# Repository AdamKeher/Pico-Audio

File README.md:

# picoAUDIO
The audio solution dedicated to the TinyPICO.

Arduino Support Library: https://github.com/AdamKeher/Pico-Audio-Arduino

3d printable base: https://github.com/AdamKeher/Pico-Audio/tree/master/base
## About
The picoAUDIO is a fully featured audio solution specially made for the TinyPICO ESP32 development board, featuring an I2S Stereo DAC, I2S Mono MEMS Microphone, builtin 3.7W Stereo Amplifier, dedicated Headphone Amplifier, I2C GPIO Extender and built-in MicroSD card reader.

We utilise a low power NXP UDA1334A IC featuring a clear digital 16/20/24 bit, 44.1kHz, stereo audio DAC. Accompanying the DAC is a Knowles SPH0645 I2S digital mono microphone. This miniature low power MEMS microphone provides a low noise, 24 bit, 44.1kHz stream. Complimenting the DAC is the powerful Maxim MAX98306 3.7W stereo class D amplifier with stero speaker terminals and a Texas Instrumets TPA6132A2 stereo headphone amplifier with 3.5mm audio jack.

A simple mounting socket hosts the TinyPICO development board and connects all of these great features together in a seamless and easy to utilise footprint measuring a tiny 33 mm x 57 mm (1.29in x 2.24in). To provide maximum connectivity the board features a built-in MicroSD card reader and GPIO extender to hookup 8 inputs and outputs for all of your button and LED needs.
## PCB Layout

## Features
The software and hardware used in this project have been made possible by the principle of open hardware and software. Many of the samples have been collected together from a variety of authors and modified to work out of the box with the picoAUDIO for instructional purposes. Please consult each sample project for relevant license and credit.
## Features
* TinyPICO Compatible
  * Simply plug your TinyPICO board into the picoAUDIO and your ready to go
* Audio Out
  * Dedicated Texas Instruments headphone amplifier for distortion free audio.
  * 3.5mm headphone jack. Plug in headphones or line out to an external device.
  * Stereo screw clamp audio terminals. The speaker terminals automatically mute when the 3.5mm jack is used.
* Built-in MicroSD Card
  * Quality Molex mechanism
  * Simple SPI interface
  * Activity LED light
  * Push-Push socket with overhanging edge mounted card for easy insertion
* UDA1334A Stereo DAC
  * Low power audio DAC
  * Integrated digital filter and switchable digital de-emphasis for 44.1 kHz frequency
  * Supports samples from 16 to 100 kHz
  * Simple I2S interface
  * 16/20/24 bit audio
  * High linearity, wide dynamic range and low distortion
* MAX98306 Stereo Amplifier
  * Low power efficient operation
  * 3.7W @ 3Ohm, 10% THD / 1.7W at 8Ohm, 10% THD
  * Spread Spectrum Modulation
  * Five selectable gain levels
  * Excellent click and pop suppression
* TPA6132A2 Headphone Amplifier
  * 25mW Headphone Amplifier for 16/32Ω Headphones with 3.5mm Audio Jack  
  * Unlike most audioboards, the picoAUDIO features a dedicated headphone amplifer
  * Doesn't use caps to drive headphone audio, reducing unwanted noise and distortion
  * Click and pop supression
  * Low power amplifier @ 2.1mA typical supply current
  * Four selectable gain levels
* SPH0645LM4H MEMS Microphone
  * Low power design
  * Simple I2S interface
  * Flat frequency response
  * 24 bit, 44.1kHz audio
  * High SNR of 65dB(A)
  * RF shielded
  * Omnidirectional
* PCF8574 GPIO Extender
  * Low standby current
  * I2C programmable
  * Latched outputs with enough current to drive LEDs
  * 8 Input and Output ports wired to a header with 3 outputs also pre wired to onboard buttons.
## Sample Projects Modified for picoAUDIO
* Stream net radio stations with MP3 support
  * I2C 2x16 character LCD and ILI93411 320x240 TFT display samples provided
* Play audio from SD card with MP3 support
* Record audio to SD card
* Realtime full duplex audio. Vocoder example receives from mic and playback from DAC.

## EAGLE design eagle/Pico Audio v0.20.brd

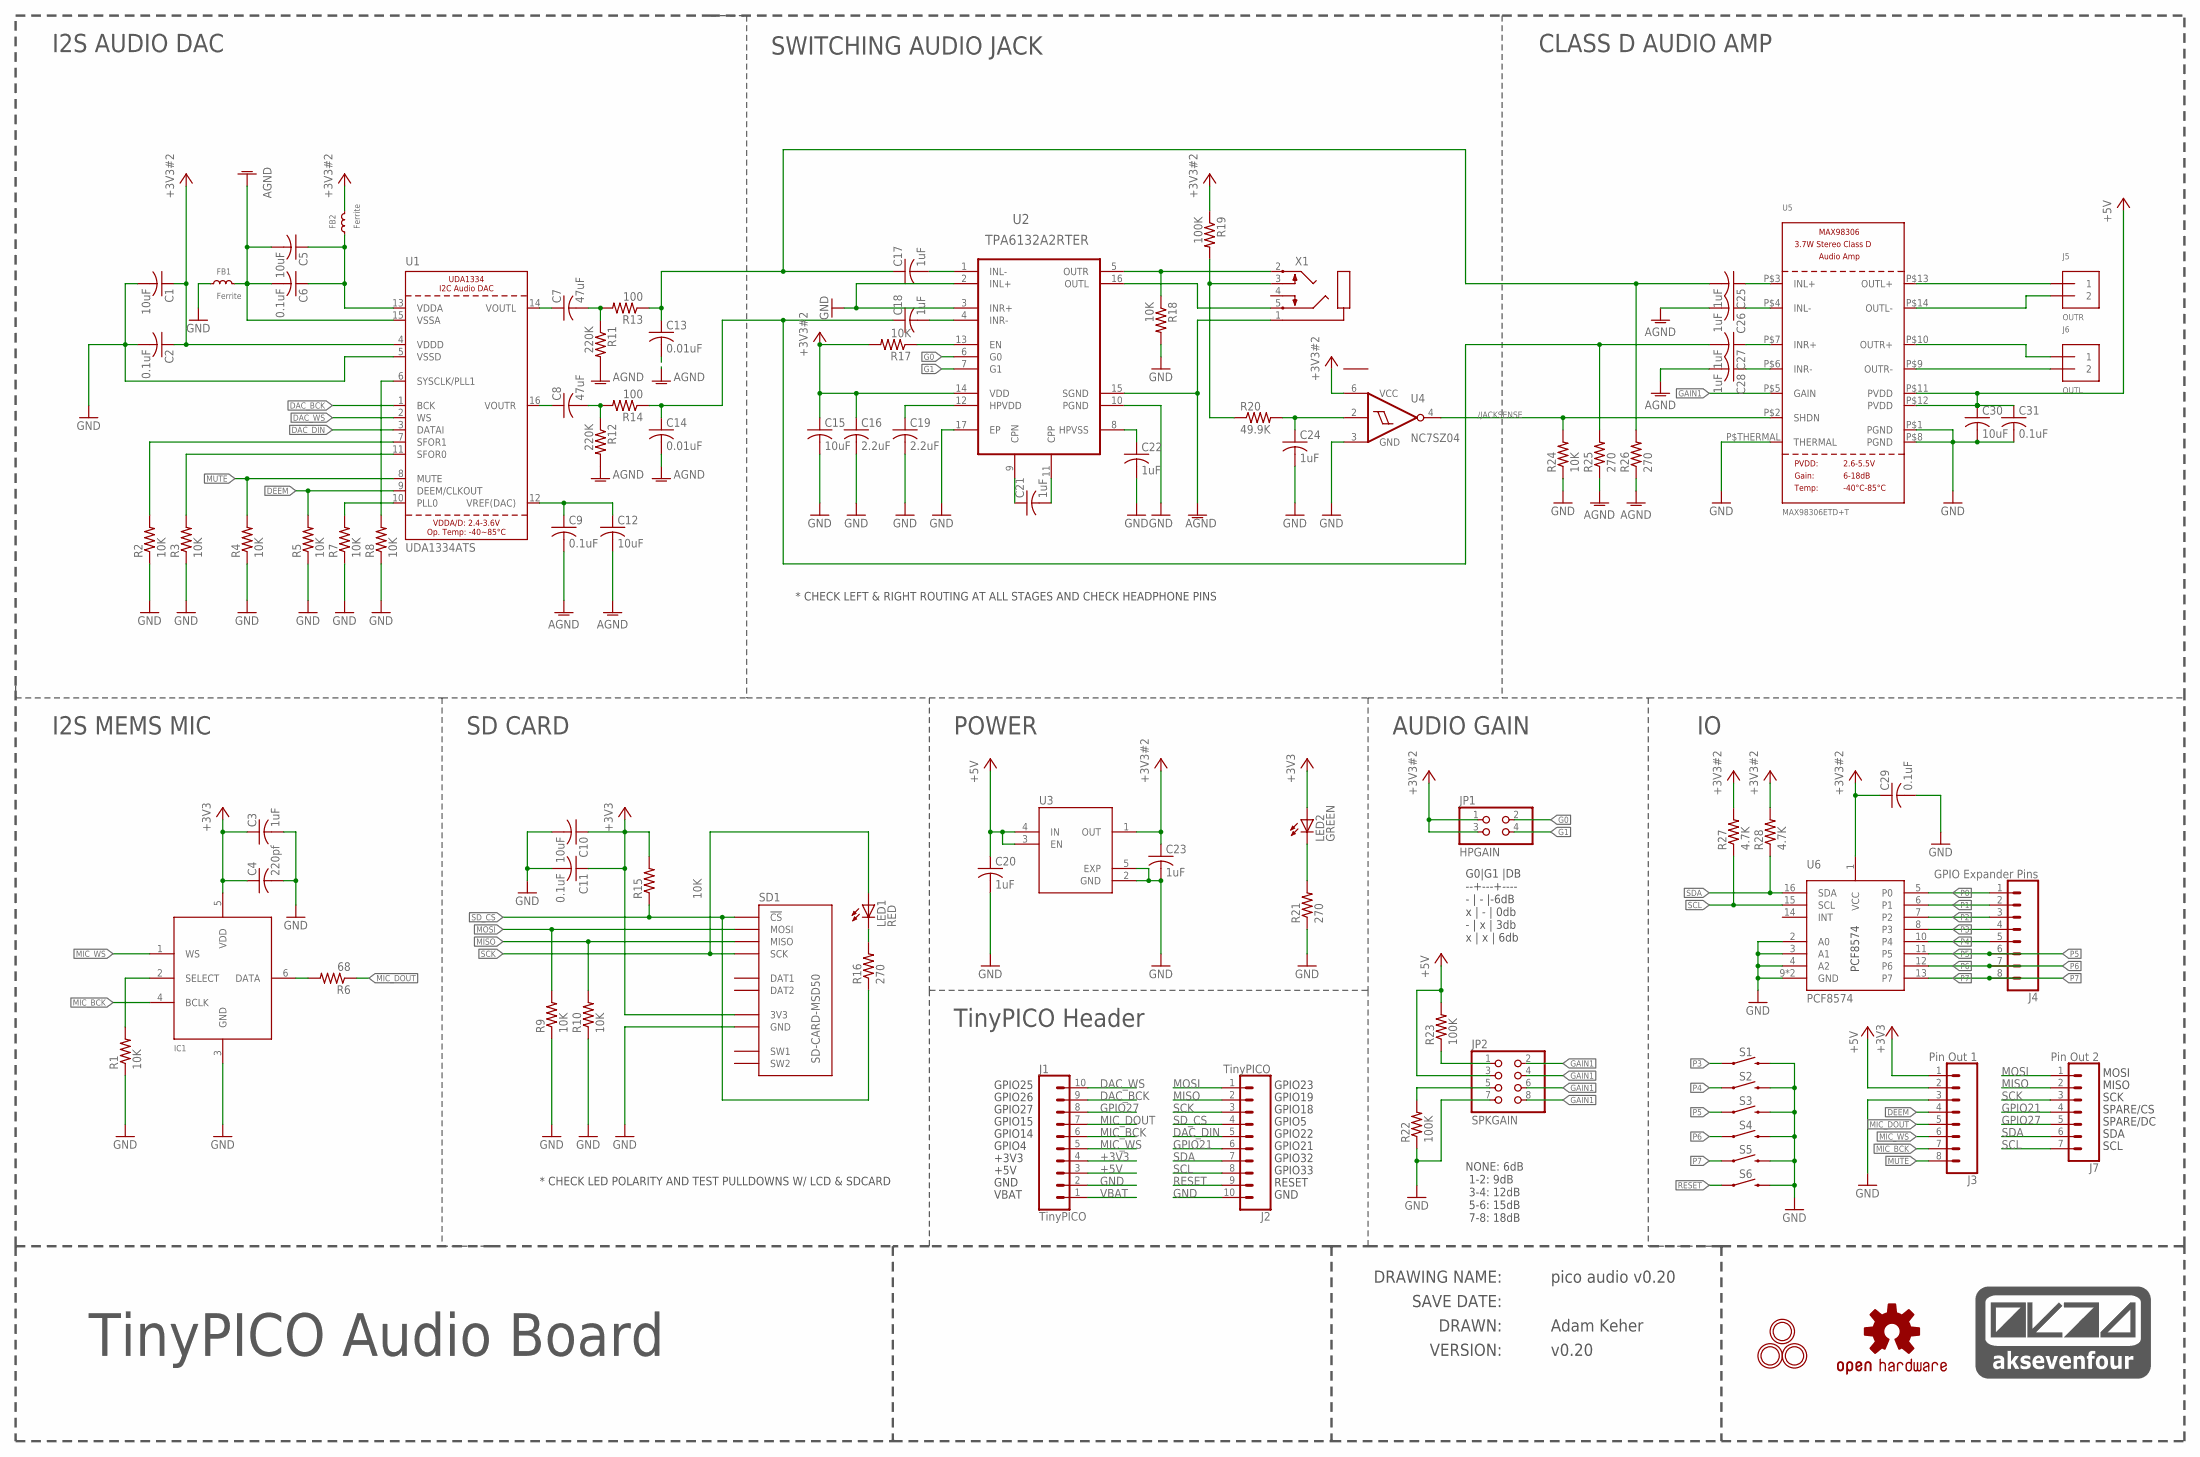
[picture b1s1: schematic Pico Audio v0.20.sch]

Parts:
AK74LOGO1: AK74_LOGOAK74_LOGO_SMALL; AK74_LOGO_MEDIUM
C1, C5, C10, C12, C15, C30: 10uF; C0603K
C2, C6, C9, C11, C29, C31: 0.1uF; C0402K
C3, C17, C18, C20, C21, C22, C23, C24, C25, C26, C27, C28: 1uF; C0402K
C4: 220pf; C0402K
C7, C8: 47uF; C1210K
C13, C14: 0.01uF; C0402K
C16, C19: 2.2uF; C0402K
FB1, FB2: Ferrite; R0805
IC1: MIC_I2S_SPH0645; SPH0645LM4H
J1, J2: TinyPICO; 1X10_NO_SILK
J3: Pin Out 1; 1X08_NO_SILK
J4: GPIO Expander Pins; 1X08_NO_SILK
J5: OUTR; TERMBLOCK_1X2-3.5MM
J6: OUTL; TERMBLOCK_1X2-3.5MM
J7: Pin Out 2; 1X07_NO_SILK
JP1: HPGAIN; 2X02
JP2: SPKGAIN; 2X04
LED1: RED; CHIP-LED0805
LED2: GREEN; CHIP-LED0805
LOGO1: OSHW-LOGOM; OSHW-LOGO-M
MH1, MH2, MH3: MOUNTINGHOLE2.5; MOUNTINGHOLE_2.5_PLATED
R1, R2, R3, R4, R5, R7, R8, R9, R10, R15, R17, R18, R24: 10K; R0402
R6: 68; R0402
R11, R12: 220K; R0402
R13, R14: 100; R0402
R16, R21, R25, R26: 270; R0402
R19, R22, R23: 100K; R0402
R20: 49.9K; R0402
R27, R28: 4.7K; R0402
S1, S2, S3, S4, S5: SKSCLDE010
S6: MOMENTARY-SWITCH-SPST-SMD-4.6X2.8MM; TACTILE_SWITCH_SMD_4.6X2.8MM
SD1: SD-CARD-MSD50; SD_5031821853
U1: UDA1334ATS; SSOP16_4.4MM
U2: TPA6132A2RTER; QFN50P300X300X80-16N
U3: NCP170AMX300TCG; VREG_NCP170AMX300TCG
U4: NC7SZ04; MICROPAK-6
U5: MAX98306ETD+T; TDFN14_3X3MM
U6: PCF8574; QFN-16-3MM
X1: STEREOJACKSTX3120-5B; STX3100

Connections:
+3V3: C3.1, C4.1, C10.1, C11.1, IC1.5 (VDD), J1.4, J3.1, LED2.A, R15.2, SD1.VCC (3V3)
+3V3#2: C1.1, C2.1, C15.1, C16.1, C23.1, C29.1, FB2.2, JP1.1, JP1.3, R17.2, R19.1, R27.2, R28.2, U1.4 (VDDD), U2.14 (VDD), U3.1 (OUT), U4.6 (VCC), U6.1 (VCC)
+5V: C20.1, C30.1, C31.1, J1.3, J3.2, JP2.3, R23.2, U3.3 (EN), U3.4 (IN), U5.P$11 (PVDD), U5.P$12 (PVDD)
/JACKSENSE: R24.2, U4.4 (Y), U5.P$2 (SHDN)
AGND: C5.2, C6.2, C9.2, C12.2, C13.2, C14.2, C26.2, C28.2, FB1.2, R11.2, R12.2, R25.1, R26.1, U1.15 (VSSA), U2.15 (SGND), X1.1
DAC_BCK: J1.9, U1.1 (BCK)
DAC_DIN: J2.5, U1.3 (DATAI)
DAC_WS: J1.10, U1.2 (WS)
DEEM: J3.4, R5.2, U1.9 (DEEM/CLKOUT)
G0: JP1.2, U2.6 (G0)
G1: JP1.4, U2.7 (G1)
GAIN1: JP2.2, JP2.4, JP2.6, JP2.8, U5.P$5 (GAIN)
GND: C1.2, C2.2, C3.2, C4.2, C10.2, C11.2, C15.2, C16.2, C19.2, C20.2, C22.2, C23.2, C24.2, C29.2, C30.2, C31.2, FB1.1, IC1.3 (GND), J1.2, J2.10, J3.3, JP2.7, R1.1, R2.1, R3.1, R4.1, R5.1, R7.1, R8.1, R9.1, R10.1, R18.2, R21.1, R22.1, R24.1, S1.3 (2), S1.4 (2), S2.3 (2), S2.4 (2), S3.3 (2), S3.4 (2), S4.3 (2), S4.4 (2), S5.3 (2), S5.4 (2), S6.3 (2), S6.4 (2), SD1.GND, U1.5 (VSSD), U2.2 (INL+), U2.3 (INR+), U2.10 (PGND), U2.17 (EP), U3.2 (GND), U3.5 (EXP), U4.3 (GND), U5.P$1 (PGND), U5.P$8 (PGND), U5.P$THERMAL (THERMAL), U6.2 (A0), U6.3 (A1), U6.4 (A2), U6.9 (GND), U6.P$1 (GND)
GPIO21: J2.6, J7.4
GPIO27: J1.8, J7.5
JACKSENSE: C24.1, R20.2, U4.2 (A)
MIC_BCK: IC1.4 (BCLK), J1.6, J3.7
MIC_DOUT: J1.7, J3.5, R6.1
MIC_WS: IC1.1 (WS), J1.5, J3.6
MISO: J2.2, J7.2, R10.2, SD1.MISO
MOSI: J2.1, J7.1, R9.2, SD1.MOSI
MUTE: J3.8, R4.2, U1.8 (MUTE)
unnamed: C5.1, C6.1, FB2.1, U1.13 (VDDA)
unnamed: C25.1, U5.P$3 (INL+)
unnamed: R2.2, U1.7 (SFOR1)
unnamed: C27.1, U5.P$7 (INR+)
unnamed: R3.2, U1.11 (SFOR0)
unnamed: C26.1, U5.P$4 (INL-)
unnamed: C28.1, U5.P$6 (INR-)
unnamed: LED2.C, R21.2
unnamed: C17.2, U2.1 (INL-)
unnamed: R7.2, U1.10 (PLL0)
unnamed: R8.2, U1.6 (SYSCLK/PLL1)
unnamed: C18.2, U2.4 (INR-)
unnamed: R17.1, U2.13 (EN)
unnamed: C9.1, C12.1, U1.12 (VREF(DAC))
unnamed: C7.1, U1.14 (VOUTL)
unnamed: C8.2, R12.1, R14.2
unnamed: J6.2, U5.P$9 (OUTR-)
unnamed: J5.2, U5.P$14 (OUTL-)
unnamed: C7.2, R11.1, R13.2
unnamed: IC1.2 (SELECT), R1.2
unnamed: C8.1, U1.16 (VOUTR)
unnamed: IC1.6 (DATA), R6.2
unnamed: C19.1, U2.12 (HPVDD)
unnamed: JP2.1, R23.1
unnamed: JP2.5, R22.2
unnamed: J5.1, U5.P$13 (OUTL+)
unnamed: LED1.C, R16.2
unnamed: J6.1, U5.P$10 (OUTR+)
unnamed: R18.1, U2.5 (OUTR), X1.2
unnamed: U2.16 (OUTL), X1.5
unnamed: C21.2, U2.11 (CPP)
unnamed: C21.1, U2.9 (CPN)
unnamed: C22.1, U2.8 (HPVSS)
unnamed: R19.2, R20.1, X1.3
P0: J4.1, U6.5 (P0)
P1: J4.2, U6.6 (P1)
P2: J4.3, U6.7 (P2)
P3: J4.4, S1.1, S1.2 (1), U6.8 (P3)
P4: J4.5, S2.1, S2.2 (1), U6.10 (P4)
P5: J4.6, S3.1, S3.2 (1), U6.11 (P5)
P6: J4.7, S4.1, S4.2 (1), U6.12 (P6)
P7: J4.8, S5.1, S5.2 (1), U6.13 (P7)
RESET: J2.9, S6.1, S6.2 (1)
SCK: J2.3, J7.3, LED1.A, SD1.SCK
SCL: J2.8, J7.7, R27.1, U6.15 (SCL)
SDA: J2.7, J7.6, R28.1, U6.16 (SDA)
SD_CS: J2.4, R15.1, R16.1, SD1.CS (!CS)
VBAT: J1.1
VOUTL: C13.1, C17.1, C25.2, R13.1, R26.2
VOUTR: C14.1, C18.1, C27.2, R14.1, R25.2

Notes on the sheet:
I2S MEMS MIC
CLASS D AUDIO AMP
I2S AUDIO DAC
SD CARD
AUDIO GAIN
SAVE DATE:
DRAWN:
VERSION:
DRAWING NAME:
NONE: 6dB 1-2: 9dB 3-4: 12dB 5-6: 15dB 7-8: 18dB
SWITCHING AUDIO JACK
SPARE/CS
MOSI
MISO
SCK
SPARE/DC
POWER
SDA
SCL
TinyPICO Header
GPIO25
GPIO26
GPIO27
GPIO15
GPIO14
GPIO4
+3V3
+5V
GND
VBAT
GPIO23
GPIO19
GPIO18
GPIO5
GPIO22
GPIO21
GPIO32
GPIO33
RESET
G0|G1 |DB --+---+---- - | - |-6dB x | - | 0db - | x | 3db x | x | 6db

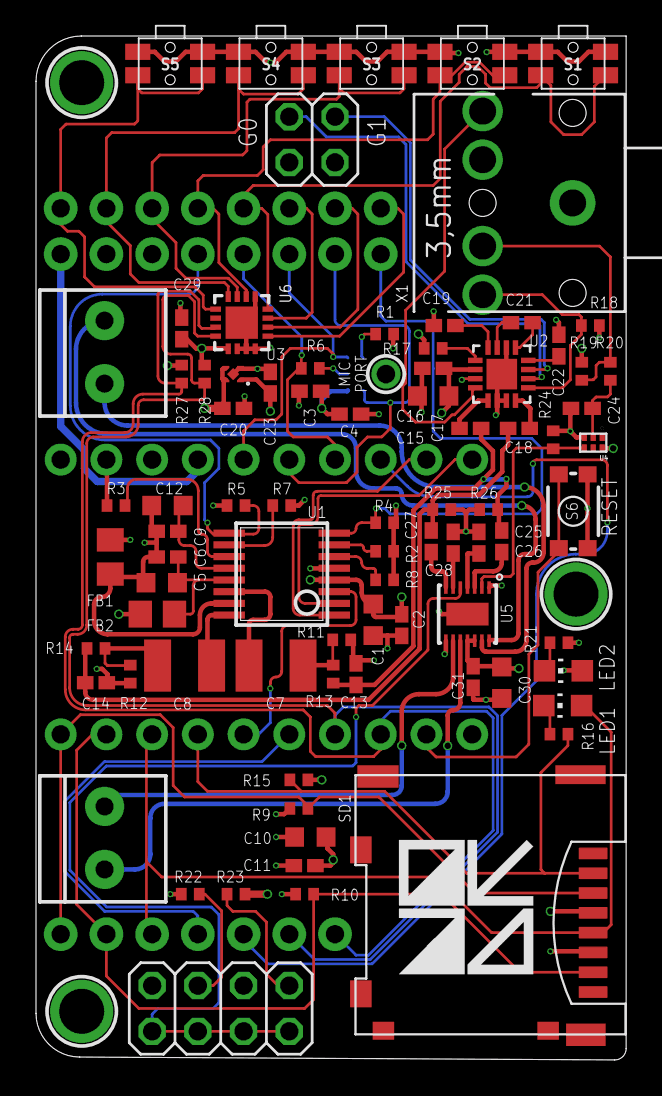
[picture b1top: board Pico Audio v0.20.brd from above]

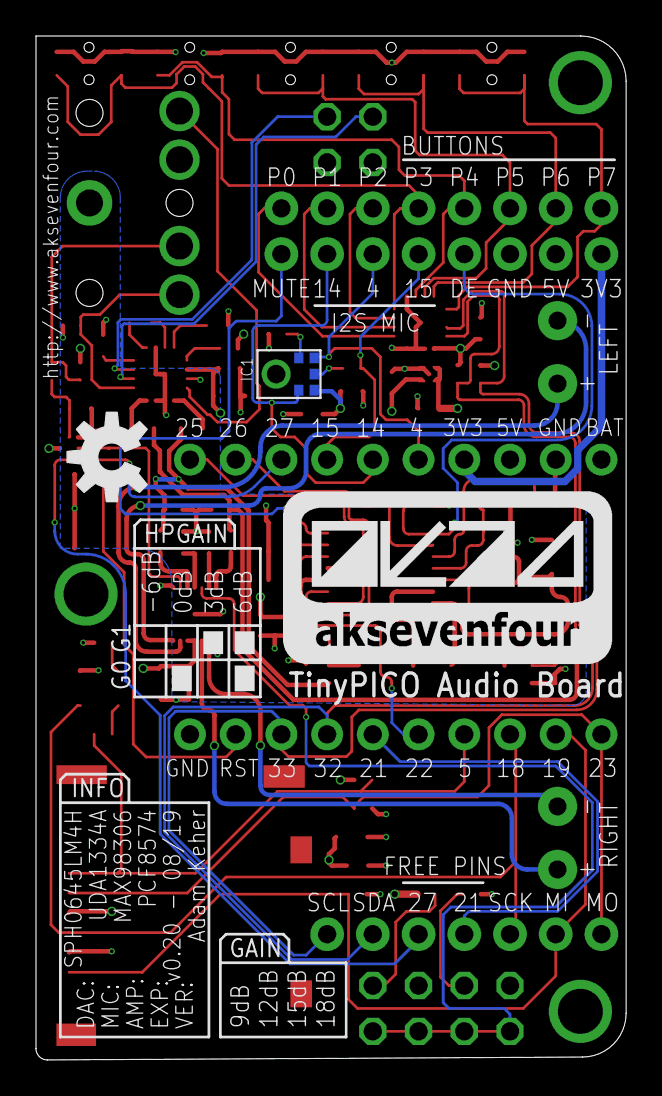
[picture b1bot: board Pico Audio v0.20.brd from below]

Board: 4 copper layers, 32.8 x 56.9 mm, 93 parts (3 on the bottom side), 71 nets.

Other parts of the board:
U$1: AK74_LOGO_MEDIUM_TEXTONLY_SQUARE

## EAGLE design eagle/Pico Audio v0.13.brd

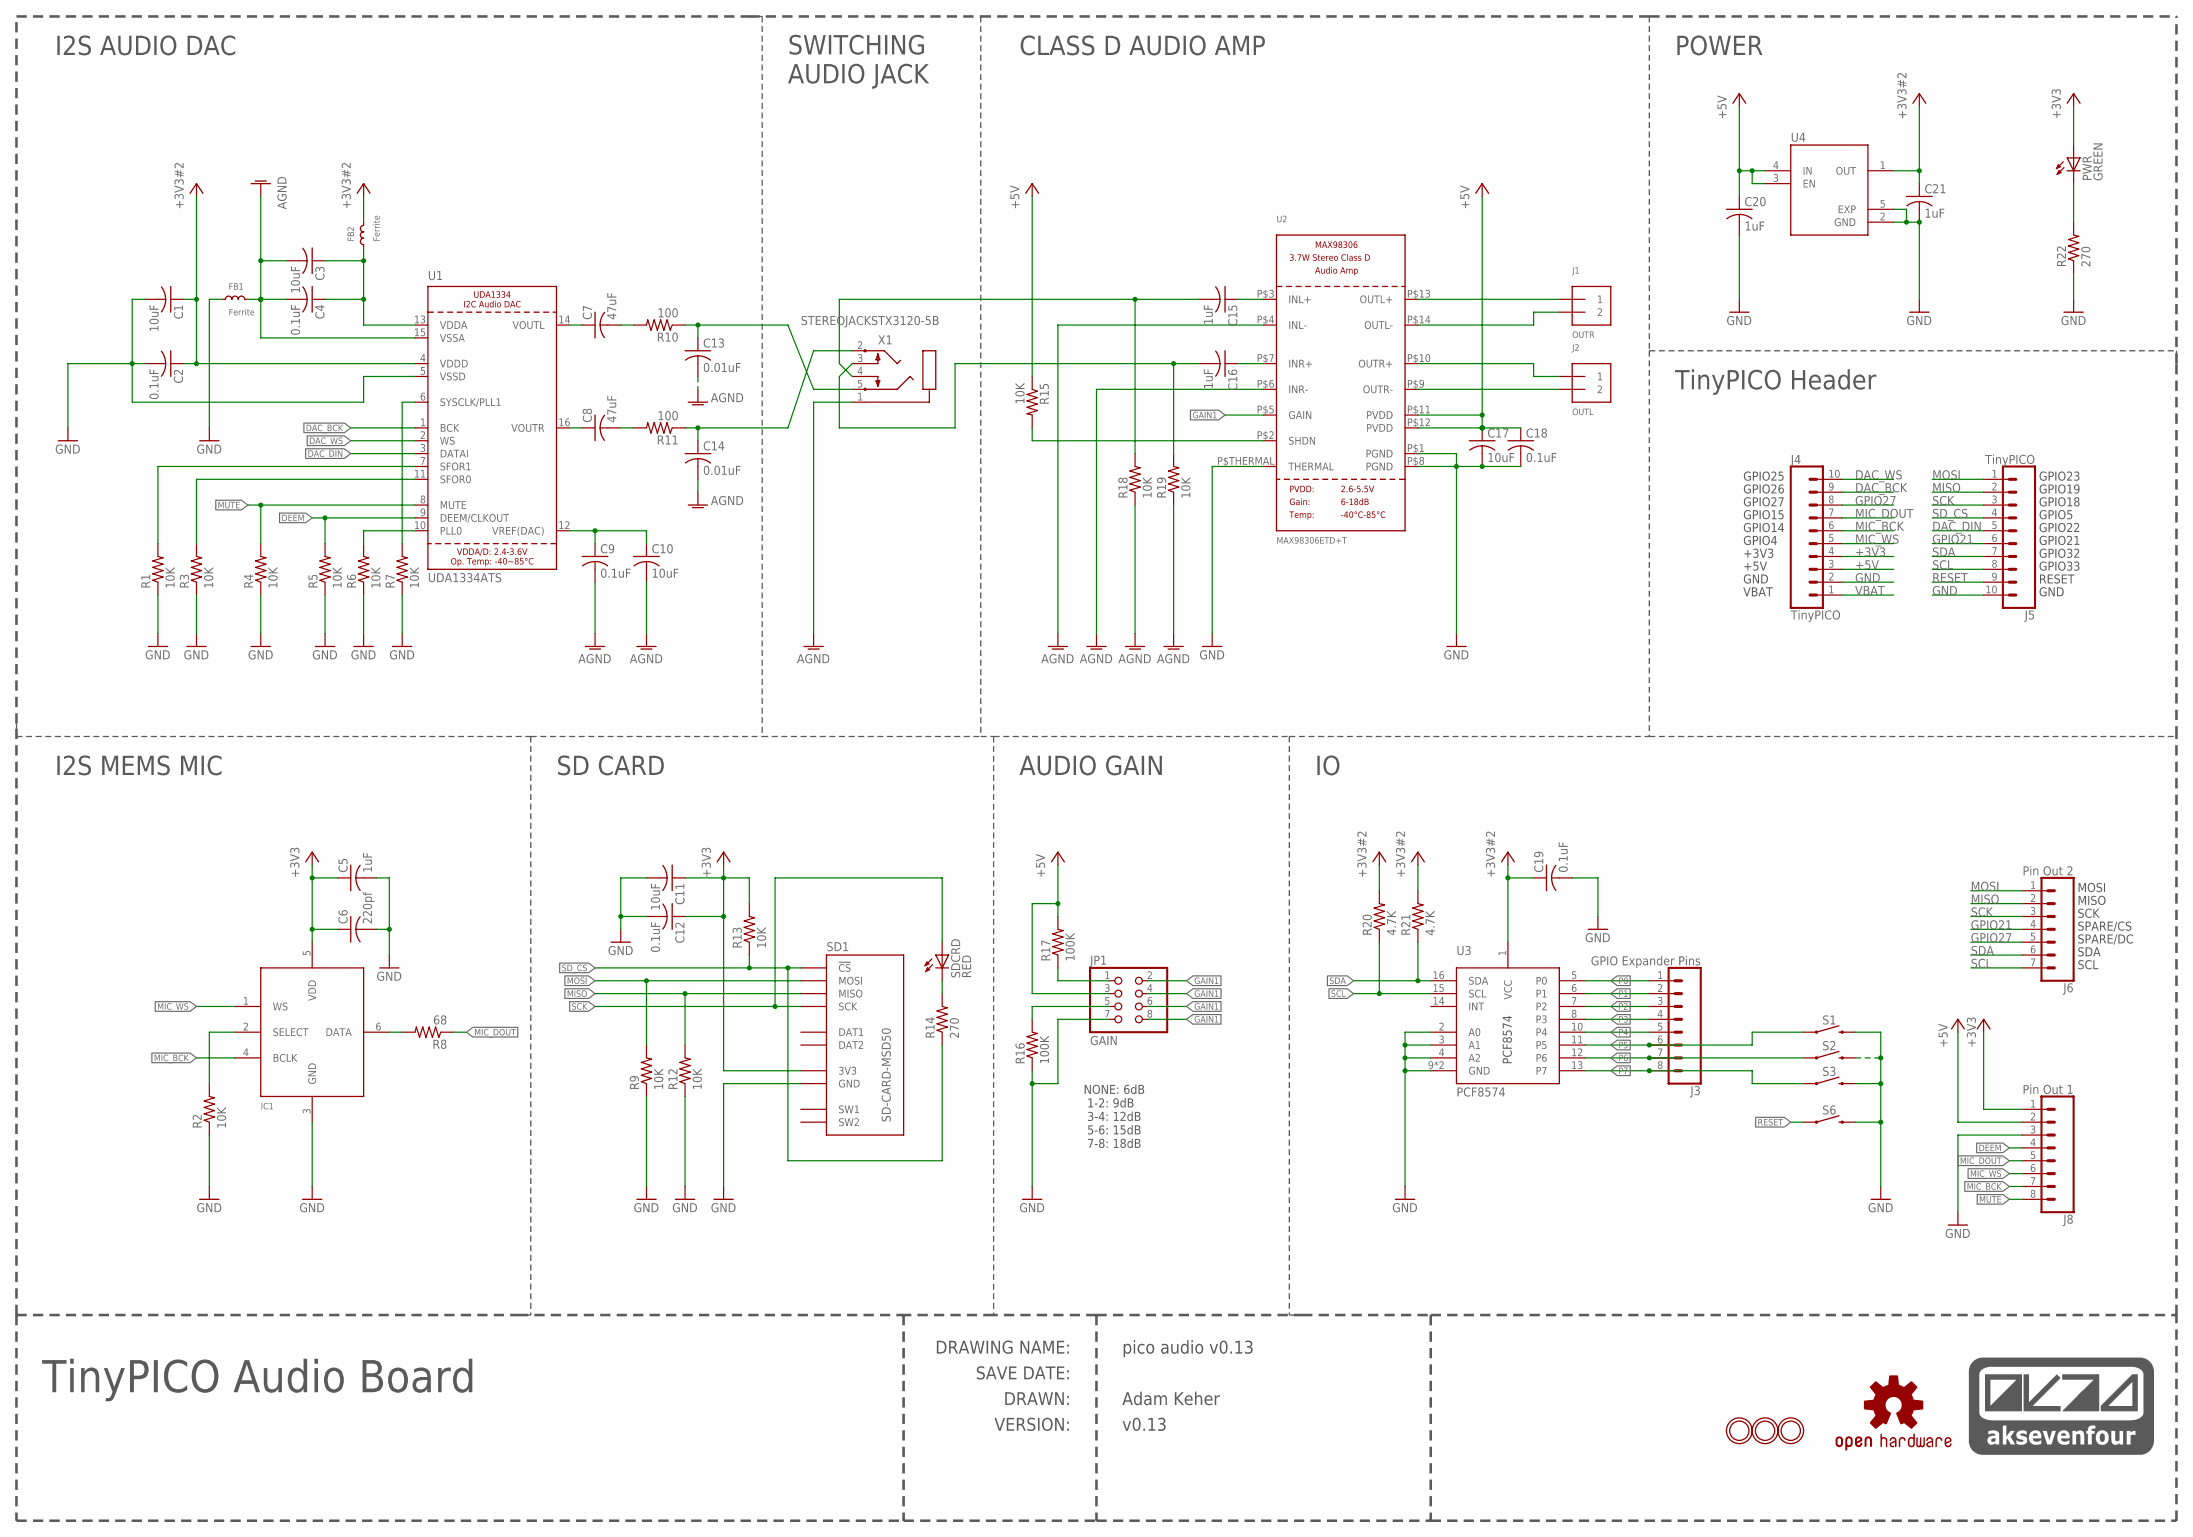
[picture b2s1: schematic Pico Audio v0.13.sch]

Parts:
AK74LOGO2: AK74_LOGOAK74_LOGO_SMALL; AK74_LOGO_MEDIUM
C1, C3, C10, C11, C17: 10uF; C0603K
C2, C4, C9, C12, C18, C19: 0.1uF; C0402K
C5, C15, C16, C20, C21: 1uF; C0402K
C6: 220pf; C0402K
C7, C8: 47uF; C1210K
C13, C14: 0.01uF; C0402K
FB1, FB2: Ferrite; R0805
IC1: MIC_I2S_SPH0645; SPH0645LM4H
J1: OUTR; TERMBLOCK_1X2-3.5MM
J2: OUTL; TERMBLOCK_1X2-3.5MM
J3: GPIO Expander Pins; 1X08_NO_SILK
J4, J5: TinyPICO; 1X10_NO_SILK
J6: Pin Out 2; 1X07_NO_SILK
J8: Pin Out 1; 1X08_NO_SILK
JP1: GAIN; 2X04
LOGO1: OSHW-LOGOM; OSHW-LOGO-M
MH1, MH2, MH3: MOUNTINGHOLE2.5; MOUNTINGHOLE_2.5_PLATED
PWR: GREEN; CHIP-LED0805
R1, R2, R3, R4, R5, R6, R7, R9, R12, R13, R15, R18, R19: 10K; R0402
R8: 68; R0402
R10, R11: 100; R0402
R14, R22: 270; R0402
R16, R17: 100K; R0402
R20, R21: 4.7K; R0402
S1, S2, S3, S6: MOMENTARY-SWITCH-SPST-SMD-4.6X2.8MM; TACTILE_SWITCH_SMD_4.6X2.8MM
SD1: SD-CARD-MSD50; SD_5031821853
SDCRD: RED; CHIP-LED0805
U1: UDA1334ATS; SSOP16_4.4MM
U2: MAX98306ETD+T; TDFN14_3X3MM
U3: PCF8574; QFN-16-3MM
U4: NCP170AMX300TCG; VREG_NCP170AMX300TCG
X1: STEREOJACKSTX3120-5B; STX3100

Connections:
+3V3: C5.1, C6.1, C11.1, C12.1, IC1.5 (VDD), J4.4, J8.1, PWR.A, R13.2, SD1.VCC (3V3)
+3V3#2: C1.1, C2.1, C19.1, C21.1, FB2.2, R20.2, R21.2, U1.4 (VDDD), U3.1 (VCC), U4.1 (OUT)
+5V: C17.1, C18.1, C20.1, J4.3, J8.2, JP1.3, R15.1, R17.2, U2.P$11 (PVDD), U2.P$12 (PVDD), U4.3 (EN), U4.4 (IN)
AGND: C3.2, C4.2, C9.2, C10.2, C13.2, C14.2, FB1.2, R18.1, R19.1, U1.15 (VSSA), U2.P$4 (INL-), U2.P$6 (INR-), X1.1
DAC_BCK: J4.9, U1.1 (BCK)
DAC_DIN: J5.5, U1.3 (DATAI)
DAC_WS: J4.10, U1.2 (WS)
DEEM: J8.4, R5.2, U1.9 (DEEM/CLKOUT)
GAIN1: JP1.2, JP1.4, JP1.6, JP1.8, U2.P$5 (GAIN)
GND: C1.2, C2.2, C5.2, C6.2, C11.2, C12.2, C17.2, C18.2, C19.2, C20.2, C21.2, FB1.1, IC1.3 (GND), J4.2, J5.10, J8.3, JP1.7, R1.1, R2.1, R3.1, R4.1, R5.1, R6.1, R7.1, R9.1, R12.1, R16.1, R22.1, S1.3 (2), S1.4 (2), S2.3 (2), S2.4 (2), S3.3 (2), S3.4 (2), S6.3 (2), S6.4 (2), SD1.GND, U1.5 (VSSD), U2.P$1 (PGND), U2.P$8 (PGND), U2.P$THERMAL (THERMAL), U3.2 (A0), U3.3 (A1), U3.4 (A2), U3.9 (GND), U3.P$1 (GND), U4.2 (GND), U4.5 (EXP)
GPIO21: J5.6, J6.4
GPIO27: J4.8, J6.5
MIC_BCK: IC1.4 (BCLK), J4.6, J8.7
MIC_DOUT: J4.7, J8.5, R8.1
MIC_WS: IC1.1 (WS), J4.5, J8.6
MISO: J5.2, J6.2, R12.2, SD1.MISO
MOSI: J5.1, J6.1, R9.2, SD1.MOSI
MUTE: J8.8, R4.2, U1.8 (MUTE)
unnamed: C3.1, C4.1, FB2.1, U1.13 (VDDA)
unnamed: C15.1, U2.P$3 (INL+)
unnamed: R1.2, U1.7 (SFOR1)
unnamed: C16.1, U2.P$7 (INR+)
unnamed: R3.2, U1.11 (SFOR0)
unnamed: PWR.C, R22.2
unnamed: R6.2, U1.10 (PLL0)
unnamed: R7.2, U1.6 (SYSCLK/PLL1)
unnamed: C9.1, C10.1, U1.12 (VREF(DAC))
unnamed: C7.1, U1.14 (VOUTL)
unnamed: C8.2, R11.2
unnamed: J2.2, U2.P$9 (OUTR-)
unnamed: J1.2, U2.P$14 (OUTL-)
unnamed: C7.2, R10.2
unnamed: IC1.2 (SELECT), R2.2
unnamed: C8.1, U1.16 (VOUTR)
unnamed: IC1.6 (DATA), R8.2
unnamed: JP1.1, R17.1
unnamed: JP1.5, R16.2
unnamed: J1.1, U2.P$13 (OUTL+)
unnamed: R14.2, SDCRD.C
unnamed: J2.1, U2.P$10 (OUTR+)
P0: J3.1, U3.5 (P0)
P1: J3.2, U3.6 (P1)
P2: J3.3, U3.7 (P2)
P3: J3.4, U3.8 (P3)
P4: J3.5, U3.10 (P4)
P5: J3.6, S1.1, S1.2 (1), U3.11 (P5)
P6: J3.7, S2.1, S2.2 (1), U3.12 (P6)
P7: J3.8, S3.1, S3.2 (1), U3.13 (P7)
RESET: J5.9, S6.1, S6.2 (1)
SCK: J5.3, J6.3, SD1.SCK, SDCRD.A
SCL: J5.8, J6.7, R20.1, U3.15 (SCL)
SDA: J5.7, J6.6, R21.1, U3.16 (SDA)
SD_CS: J5.4, R13.1, R14.1, SD1.CS (!CS)
SHUTDOWN: R15.2, U2.P$2 (SHDN)
VBAT: J4.1
VINL: C15.2, R18.2, X1.4
VINR: C16.2, R19.2, X1.3
VOUTL: C13.1, R10.1, X1.5
VOUTR: C14.1, R11.1, X1.2

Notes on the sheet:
I2S MEMS MIC
CLASS D AUDIO AMP
I2S AUDIO DAC
SD CARD
AUDIO GAIN
SAVE DATE:
DRAWN:
VERSION:
DRAWING NAME:
NONE: 6dB 1-2: 9dB 3-4: 12dB 5-6: 15dB 7-8: 18dB
SWITCHING AUDIO JACK
SPARE/CS
MOSI
MISO
SCK
SPARE/DC
POWER
SDA
SCL
TinyPICO Header
GPIO25
GPIO26
GPIO27
GPIO15
GPIO14
GPIO4
+3V3
+5V
GND
VBAT
GPIO23
GPIO19
GPIO18
GPIO5
GPIO22
GPIO21
GPIO32
GPIO33
RESET

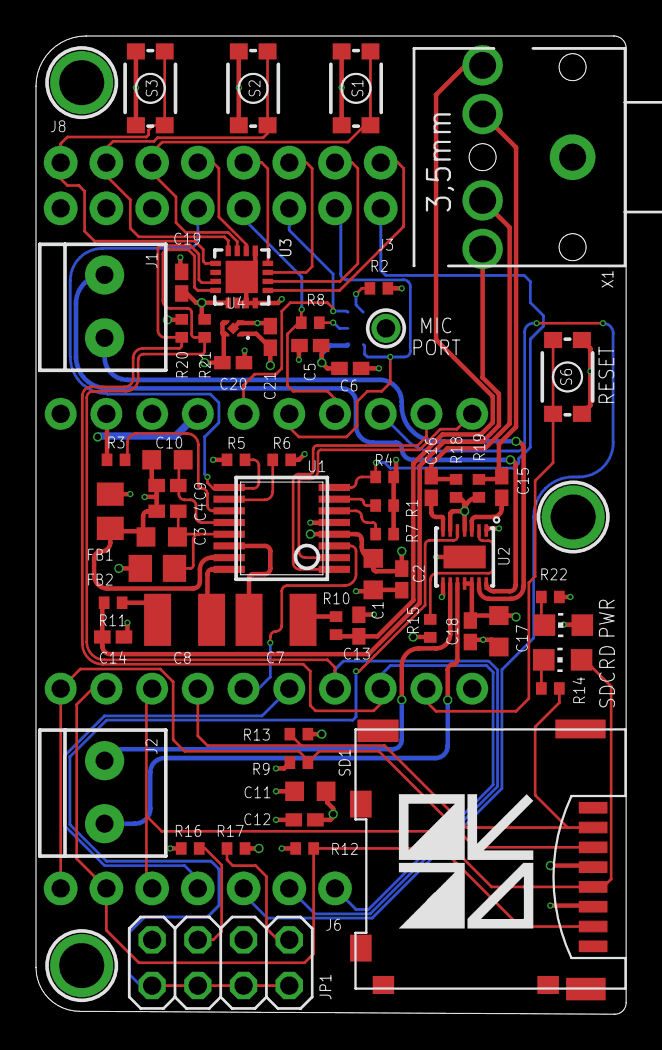
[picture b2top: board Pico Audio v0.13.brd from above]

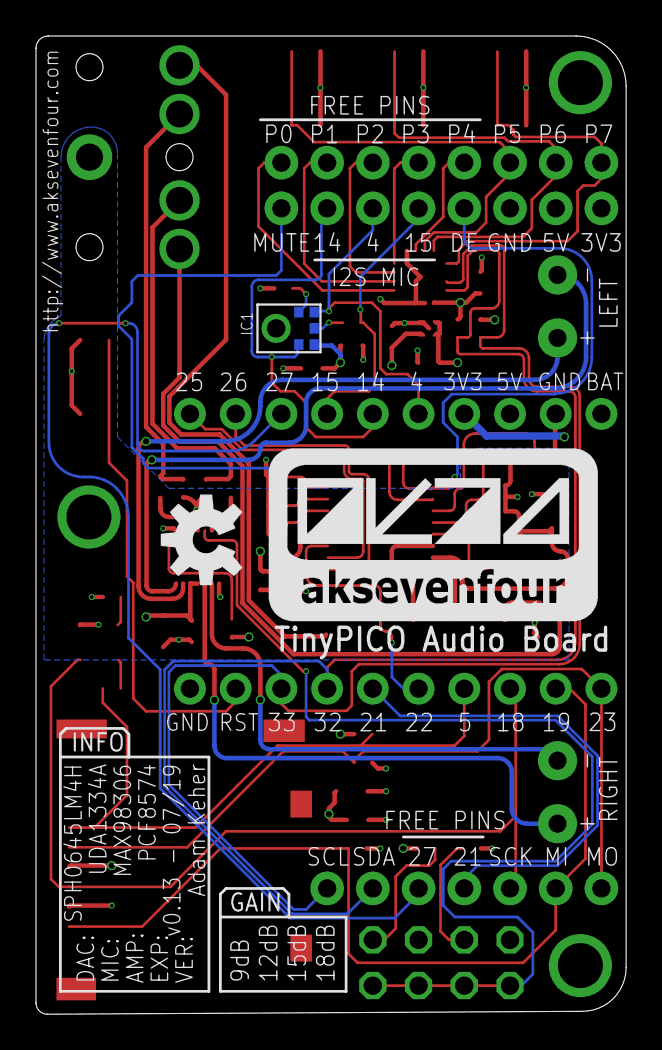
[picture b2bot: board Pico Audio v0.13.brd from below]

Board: 4 copper layers, 32.8 x 54.3 mm, 72 parts (3 on the bottom side), 58 nets.

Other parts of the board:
U$1: AK74_LOGO_MEDIUM_TEXTONLY_SQUARE

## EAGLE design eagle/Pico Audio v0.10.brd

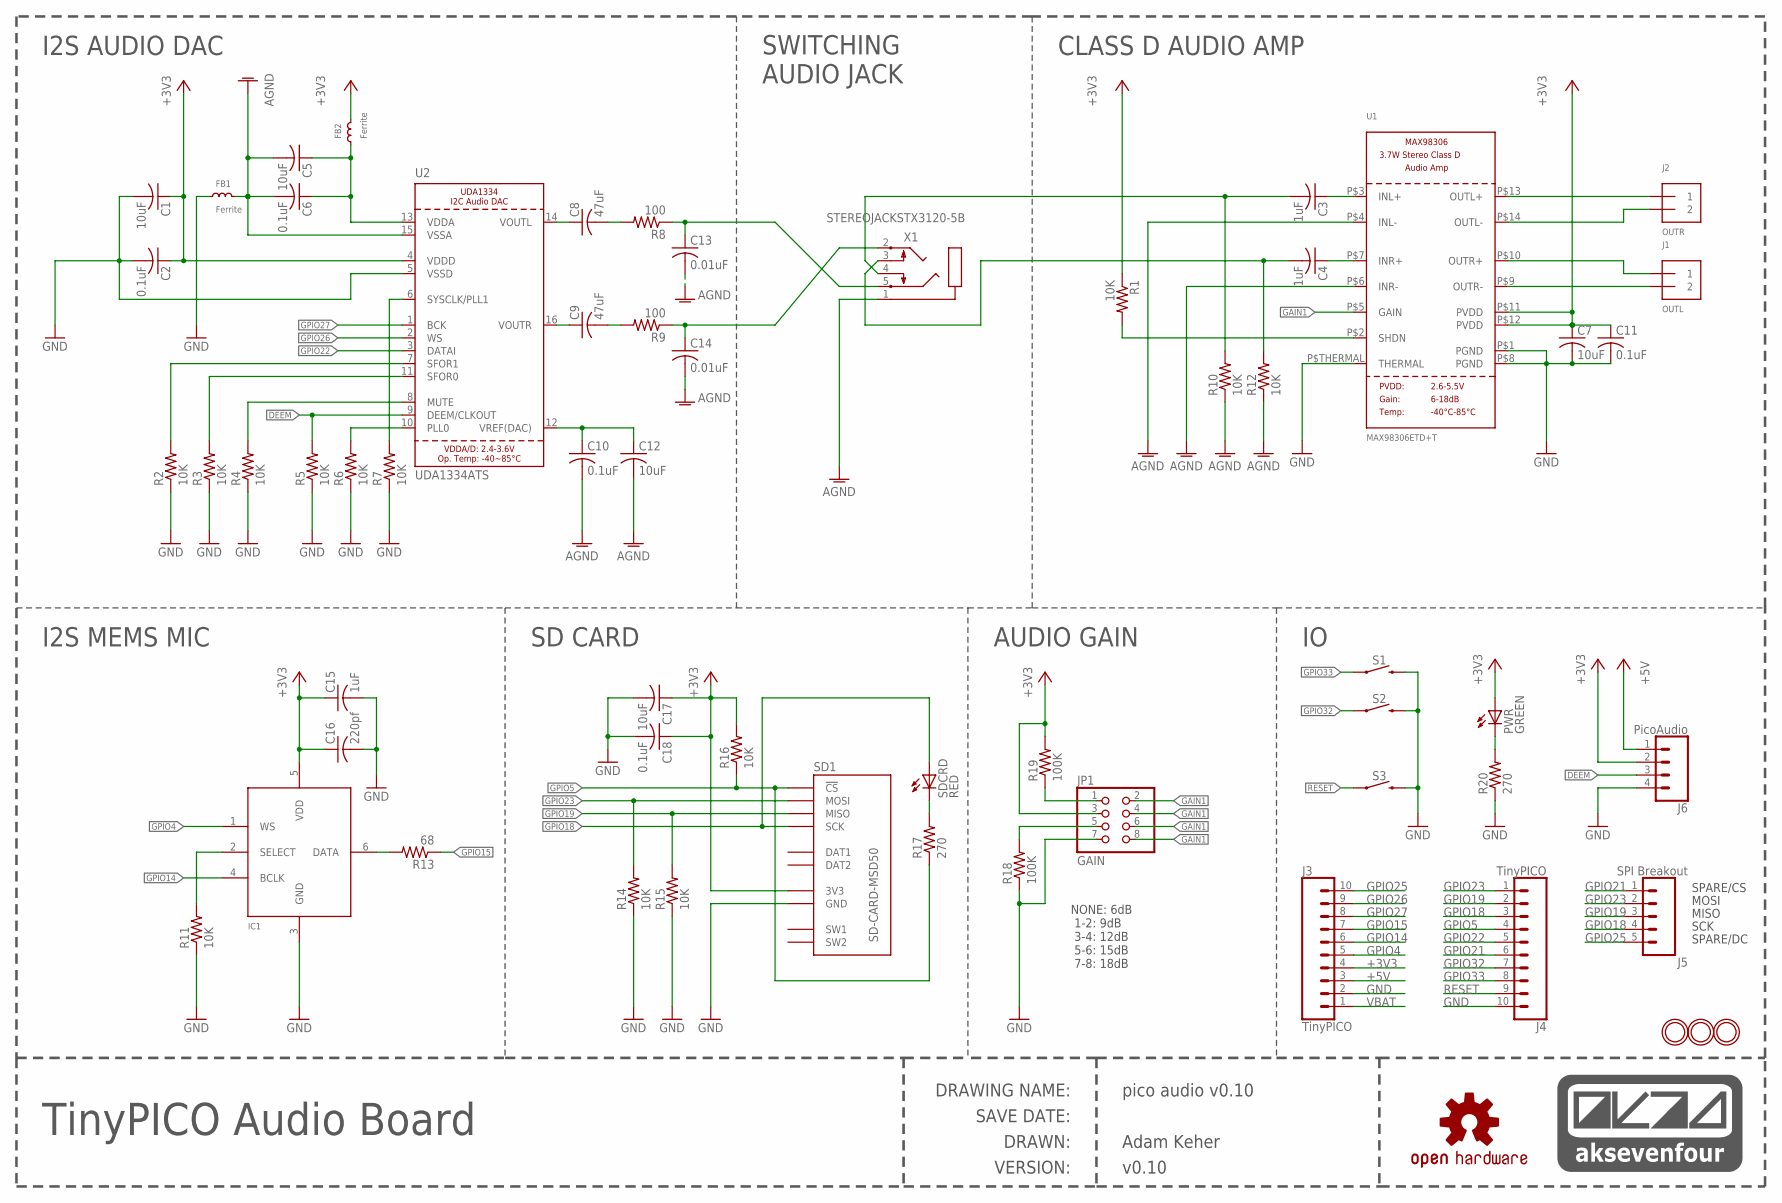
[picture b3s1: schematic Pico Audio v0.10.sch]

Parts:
AK74LOGO2: AK74_LOGO; AK74_LOGO_MEDIUM_TEXTONLY
C1, C5, C7, C12, C17: 10uF; C0603K
C2, C6, C10, C11, C18: 0.1uF; C0402K
C3, C4, C15: 1uF; C0402K
C8, C9: 47uF; C1210K
C13, C14: 0.01uF; C0402K
C16: 220pf; C0402K
FB1, FB2: Ferrite; R0805
IC1: MIC_I2S_SPH0645; SPH0645LM4H
J1: OUTL; TERMBLOCK_1X2-3.5MM
J2: OUTR; TERMBLOCK_1X2-3.5MM
J3, J4: TinyPICO; 1X10_NO_SILK
J5: SPI Breakout; 1X05_NO_SILK
J6: PicoAudio; 1X04_NO_SILK
JP1: GAIN; 2X04
LOGO2: OSHW-LOGOM; OSHW-LOGO-M
PWR: GREEN; CHIP-LED0805
R1, R2, R3, R4, R5, R6, R7, R10, R11, R12, R14, R15, R16: 10K; R0402
R8, R9: 100; R0402
R13: 68; R0402
R17, R20: 270; R0402
R18, R19: 100K; R0402
S1, S2, S3: MOMENTARY-SWITCH-SPST-SMD-4.6X2.8MM; TACTILE_SWITCH_SMD_4.6X2.8MM
SD1: SD-CARD-MSD50; SD_5031821853
SDCRD: RED; CHIP-LED0805
U1: MAX98306ETD+T; TDFN14_3X3MM
U2: UDA1334ATS; SSOP16_4.4MM
U$12, U$13, U$14: MOUNTINGHOLE2.5; MOUNTINGHOLE_2.5_PLATED
X1: STEREOJACKSTX3120-5B; STX3100

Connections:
+3V3: C1.1, C2.1, C7.1, C11.1, C15.1, C16.1, C17.1, C18.1, FB2.2, IC1.5 (VDD), J3.4, J6.2, JP1.3, PWR.A, R1.1, R16.2, R19.2, SD1.VCC (3V3), U1.P$11 (PVDD), U1.P$12 (PVDD), U2.4 (VDDD)
+5V: J3.3, J6.1
AGND: C5.2, C6.2, C10.2, C12.2, C13.2, C14.2, FB1.2, R10.1, R12.1, U1.P$4 (INL-), U1.P$6 (INR-), U2.15 (VSSA), X1.1
DEEM: J6.3, R5.2, U2.9 (DEEM/CLKOUT)
GAIN1: JP1.2, JP1.4, JP1.6, JP1.8, U1.P$5 (GAIN)
GND: C1.2, C2.2, C7.2, C11.2, C15.2, C16.2, C17.2, C18.2, FB1.1, IC1.3 (GND), J3.2, J4.10, J6.4, JP1.7, R2.1, R3.1, R4.1, R5.1, R6.1, R7.1, R11.1, R14.1, R15.1, R18.1, R20.1, S1.3 (2), S1.4 (2), S2.3 (2), S2.4 (2), S3.3 (2), S3.4 (2), SD1.GND, U1.P$1 (PGND), U1.P$8 (PGND), U1.P$THERMAL (THERMAL), U2.5 (VSSD)
GPIO4: IC1.1 (WS), J3.5
GPIO5: J4.4, R16.1, R17.1, SD1.CS (!CS)
GPIO14: IC1.4 (BCLK), J3.6
GPIO15: J3.7, R13.1
GPIO18: J4.3, J5.4, SD1.SCK, SDCRD.A
GPIO19: J4.2, J5.3, R15.2, SD1.MISO
GPIO21: J4.6, J5.1
GPIO22: J4.5, U2.3 (DATAI)
GPIO23: J4.1, J5.2, R14.2, SD1.MOSI
GPIO25: J3.10, J5.5
GPIO26: J3.9, U2.2 (WS)
GPIO27: J3.8, U2.1 (BCK)
GPIO32: J4.7, S2.1, S2.2 (1)
GPIO33: J4.8, S1.1, S1.2 (1)
unnamed: C5.1, C6.1, FB2.1, U2.13 (VDDA)
unnamed: C3.1, U1.P$3 (INL+)
unnamed: R2.2, U2.7 (SFOR1)
unnamed: C4.1, U1.P$7 (INR+)
unnamed: R3.2, U2.11 (SFOR0)
unnamed: R4.2, U2.8 (MUTE)
unnamed: PWR.C, R20.2
unnamed: R6.2, U2.10 (PLL0)
unnamed: R7.2, U2.6 (SYSCLK/PLL1)
unnamed: C10.1, C12.1, U2.12 (VREF(DAC))
unnamed: C8.1, U2.14 (VOUTL)
unnamed: C9.2, R9.2
unnamed: J1.2, U1.P$9 (OUTR-)
unnamed: J2.2, U1.P$14 (OUTL-)
unnamed: C8.2, R8.2
unnamed: IC1.2 (SELECT), R11.2
unnamed: C9.1, U2.16 (VOUTR)
unnamed: IC1.6 (DATA), R13.2
unnamed: JP1.1, R19.1
unnamed: JP1.5, R18.2
unnamed: J2.1, U1.P$13 (OUTL+)
unnamed: R17.2, SDCRD.C
unnamed: J1.1, U1.P$10 (OUTR+)
RESET: J4.9, S3.1, S3.2 (1)
SHUTDOWN: R1.2, U1.P$2 (SHDN)
VBAT: J3.1
VINL: C3.2, R10.2, X1.4
VINR: C4.2, R12.2, X1.3
VOUTL: C13.1, R8.1, X1.5
VOUTR: C14.1, R9.1, X1.2

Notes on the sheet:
I2S MEMS MIC
CLASS D AUDIO AMP
I2S AUDIO DAC
SD CARD
AUDIO GAIN
SAVE DATE:
DRAWN:
VERSION:
DRAWING NAME:
NONE: 6dB 1-2: 9dB 3-4: 12dB 5-6: 15dB 7-8: 18dB
SWITCHING AUDIO JACK
SPARE/CS
MOSI
MISO
SCK
SPARE/DC

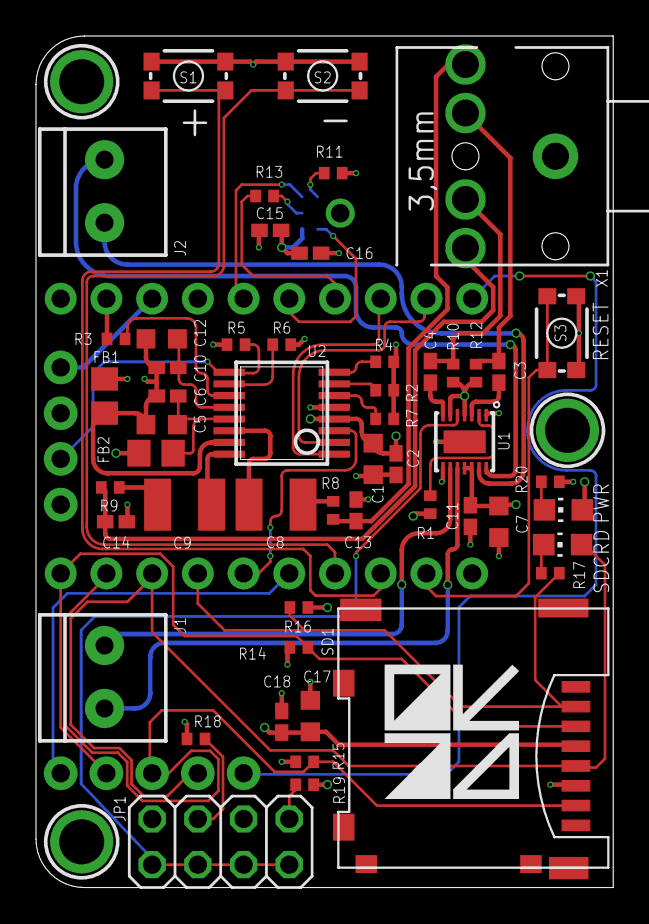
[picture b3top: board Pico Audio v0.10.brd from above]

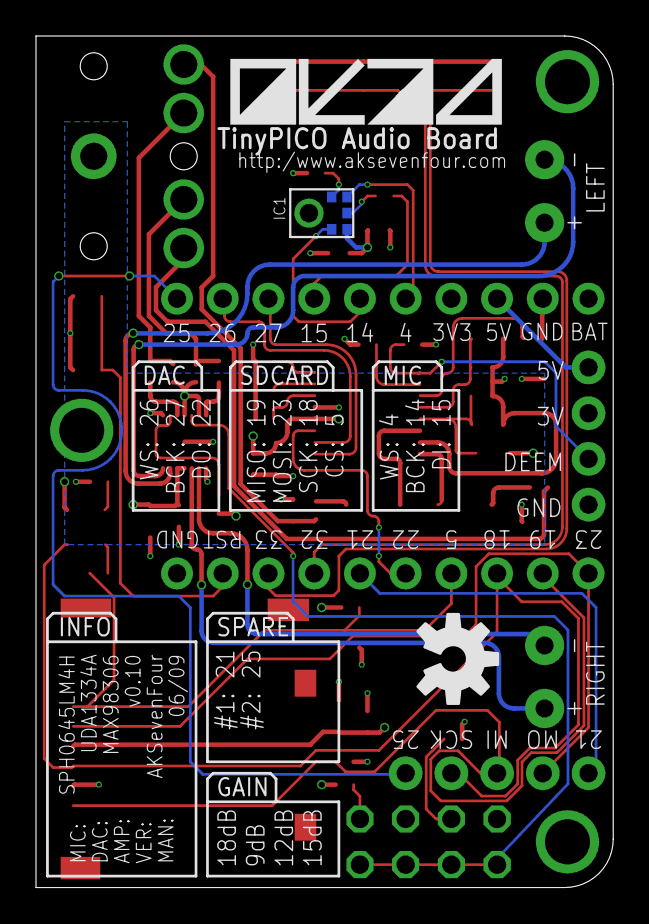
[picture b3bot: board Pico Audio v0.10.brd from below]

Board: 4 copper layers, 32.1 x 47.3 mm, 63 parts (3 on the bottom side), 49 nets.

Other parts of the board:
U$1: AK74_LOGO_MEDIUM_TEXTONLY_SQUARE

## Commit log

2019-07-16 v0.13 Update
2019-09-19 Initial Arduino library commit
    Framework for picoAUDIO library
2019-09-19 Initial Arduino library commit
2019-09-20 Move Arduino code
2019-09-21 Board Update
2019-09-21 Revert "Board Update"
    This reverts commit 64f88ad06b88c25f0d87ce8718a64f2d2cec739c.
2019-09-21 v0.20 Update
2019-09-23 Added 3d printable base
2019-09-23 3d printable base
2019-09-23 Updated base
2019-10-03 Added Shrouds

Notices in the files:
parts and their libraries:
SparkFun-Aesthetics: Licensing: Creative Commons ShareAlike 4.0 International - https://creativecommons.org/licenses/by-sa/4.0
microbuilder: This work is placed in the public domain, and may be freely used for commercial and non-commercial work with the following conditions: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
